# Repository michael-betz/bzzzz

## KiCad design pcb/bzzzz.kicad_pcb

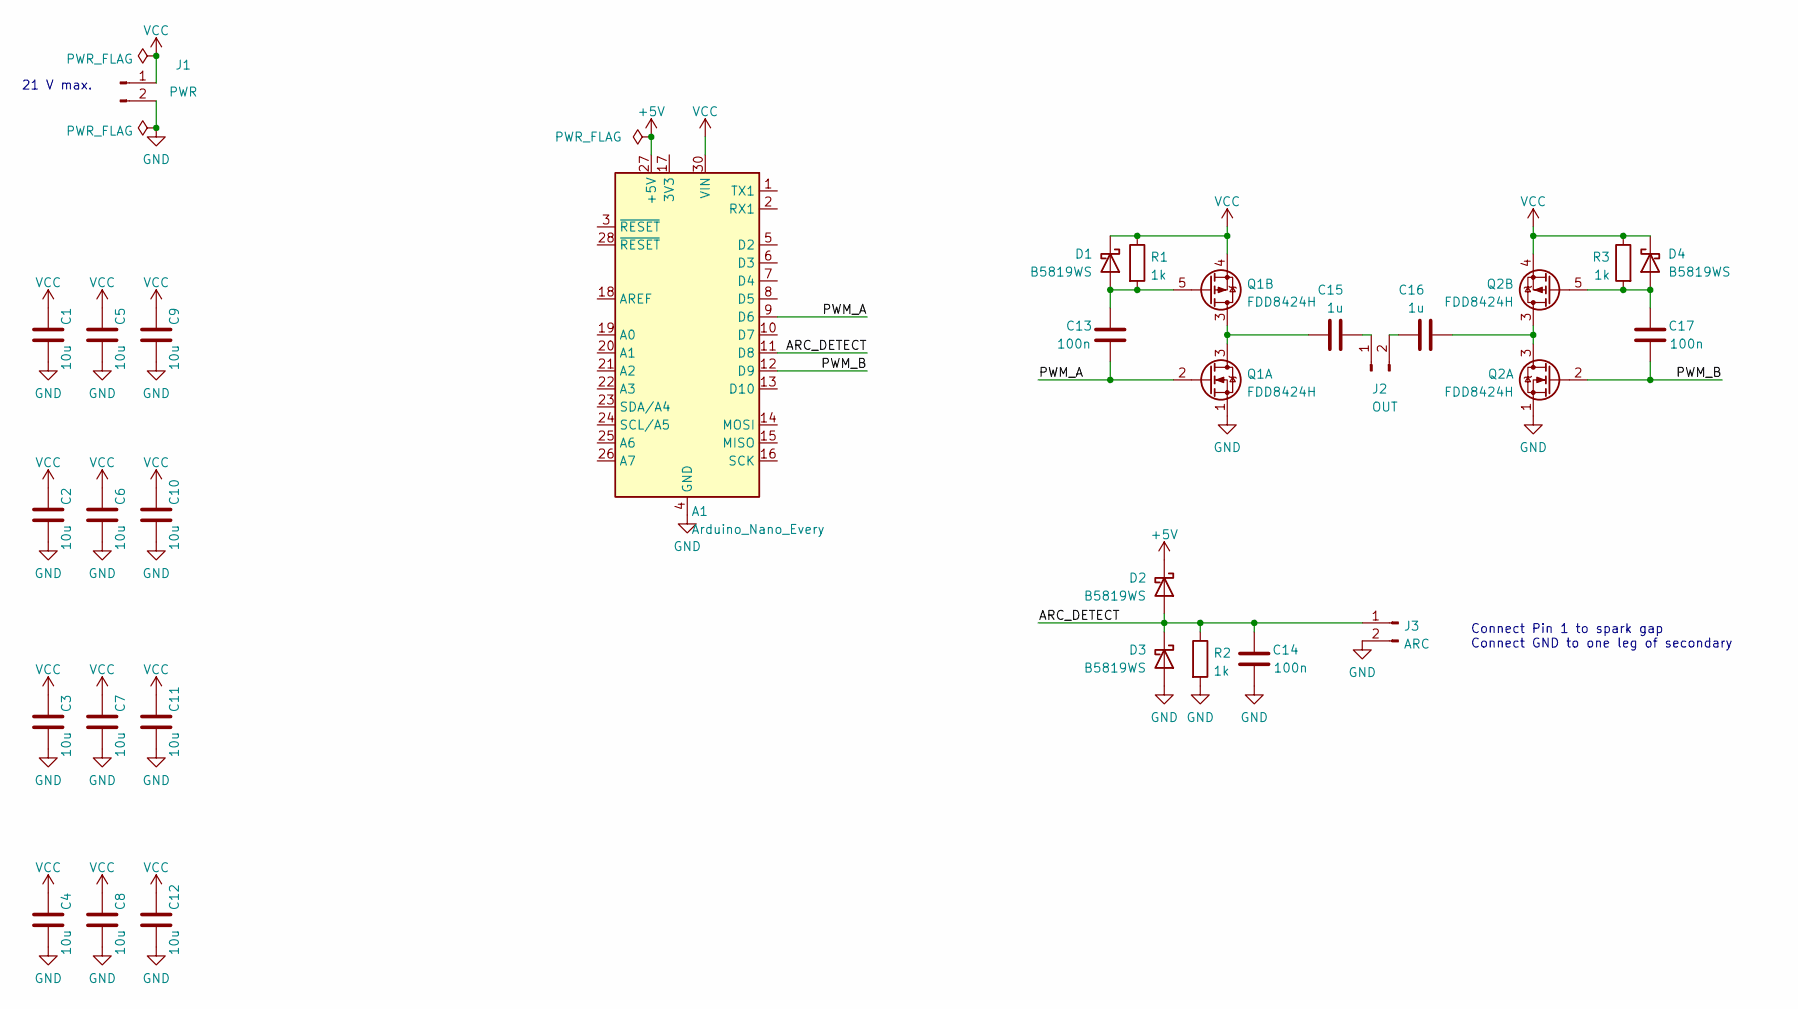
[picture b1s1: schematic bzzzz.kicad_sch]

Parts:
A1: Arduino_Nano_Every; Arduino_Nano
C1, C2, C3, C4, C5, C6, C7, C8, C9, C10, C11, C12: 10u; C_0805_2012Metric
C13, C14, C17: 100n; C_0805_2012Metric
C15, C16: 1u; C_1812_4532Metric
D1, D2, D3, D4: B5819WS; D_SOD-323_HandSoldering
J1: PWR; PinHeader_1x02_P2.54mm_Horizontal
J2: OUT; PinHeader_1x02_P2.54mm_Horizontal
J3: ARC; PinHeader_1x02_P2.54mm_Horizontal
Q1, Q2: FDD8424H; TO-252-4
R1, R2, R3: 1k; R_0805_2012Metric

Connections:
+5V: A1.27 (+5V), D2.1 (K)
/ARC_DETECT: A1.11 (D8), C14.1, D2.2 (A), D3.1 (K), J3.1, R2.1
/PWM_A: A1.9 (D6), C13.2, Q1.2 (G)
/PWM_B: A1.12 (D9), C17.2, Q2.2 (G)
GND: A1.4 (GND), A1.29 (GND), C1.2, C2.2, C3.2, C4.2, C5.2, C6.2, C7.2, C8.2, C9.2, C10.2, C11.2, C12.2, C14.2, D3.2 (A), J1.2, J3.2, Q1.1 (S), Q2.1 (S), R2.2
unnamed: C13.1, D1.2 (A), Q1.5 (G), R1.2
unnamed: C15.1, Q1.3 (D)
unnamed: C15.2, J2.1
unnamed: C16.1, J2.2
unnamed: C16.2, Q2.3 (D)
unnamed: C17.1, D4.2 (A), Q2.5 (G), R3.2
VCC: A1.30 (VIN), C1.1, C2.1, C3.1, C4.1, C5.1, C6.1, C7.1, C8.1, C9.1, C10.1, C11.1, C12.1, D1.1 (K), D4.1 (K), J1.1, Q1.4 (S), Q2.4 (S), R1.1, R3.1

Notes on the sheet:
Connect Pin 1 to spark gap Connect GND to one leg of secondary
21 V max.

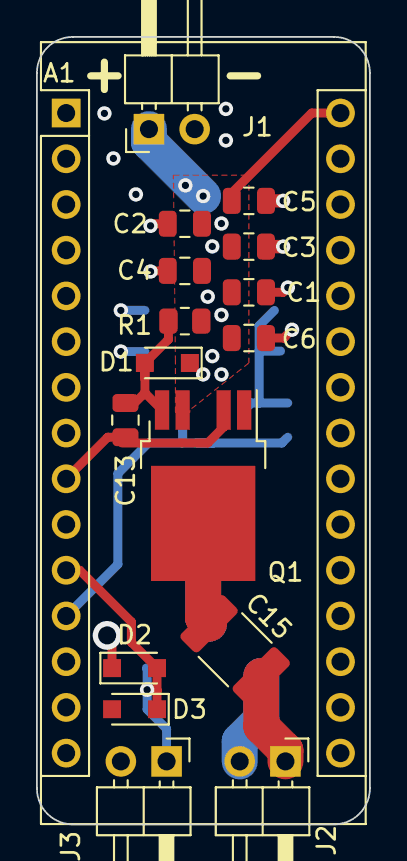
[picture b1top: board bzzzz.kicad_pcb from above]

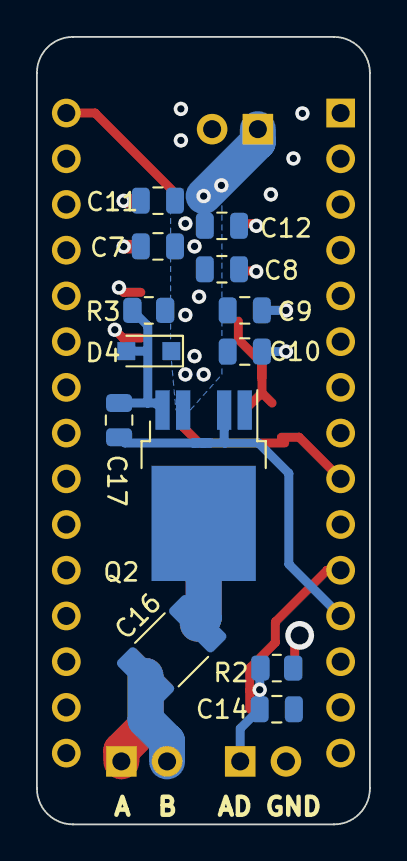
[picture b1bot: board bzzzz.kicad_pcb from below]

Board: 2 copper layers, 18.5 x 43.8 mm, 30 parts (13 on the bottom side), 12 nets.

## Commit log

2023-07-04 add arc detector
2023-08-21 add a schematic
2023-08-25 pcb: routing finished of a nice symmetric full-bridge
    PCB fits below Arduino
    Still need to choose smaller connectors
2023-09-28 pcb ordered from jlc
2023-09-28 smoke test of H-bridge board, looking good
2023-10-01 generate glitch-free phase shifted drive signals
2023-10-01 Use Timer1 so frequency can be adjusted (with TOP)
2026-03-23 comments
2026-03-23 add 4 bit dithering which works nicely
2026-03-23 add simplex noise
    there is a little state machine, making a particular interesting
    power value sticky for a minute
2026-03-23 add a second octave
2026-03-24 final config for the neon one
2026-03-31 final values for sebs neon
